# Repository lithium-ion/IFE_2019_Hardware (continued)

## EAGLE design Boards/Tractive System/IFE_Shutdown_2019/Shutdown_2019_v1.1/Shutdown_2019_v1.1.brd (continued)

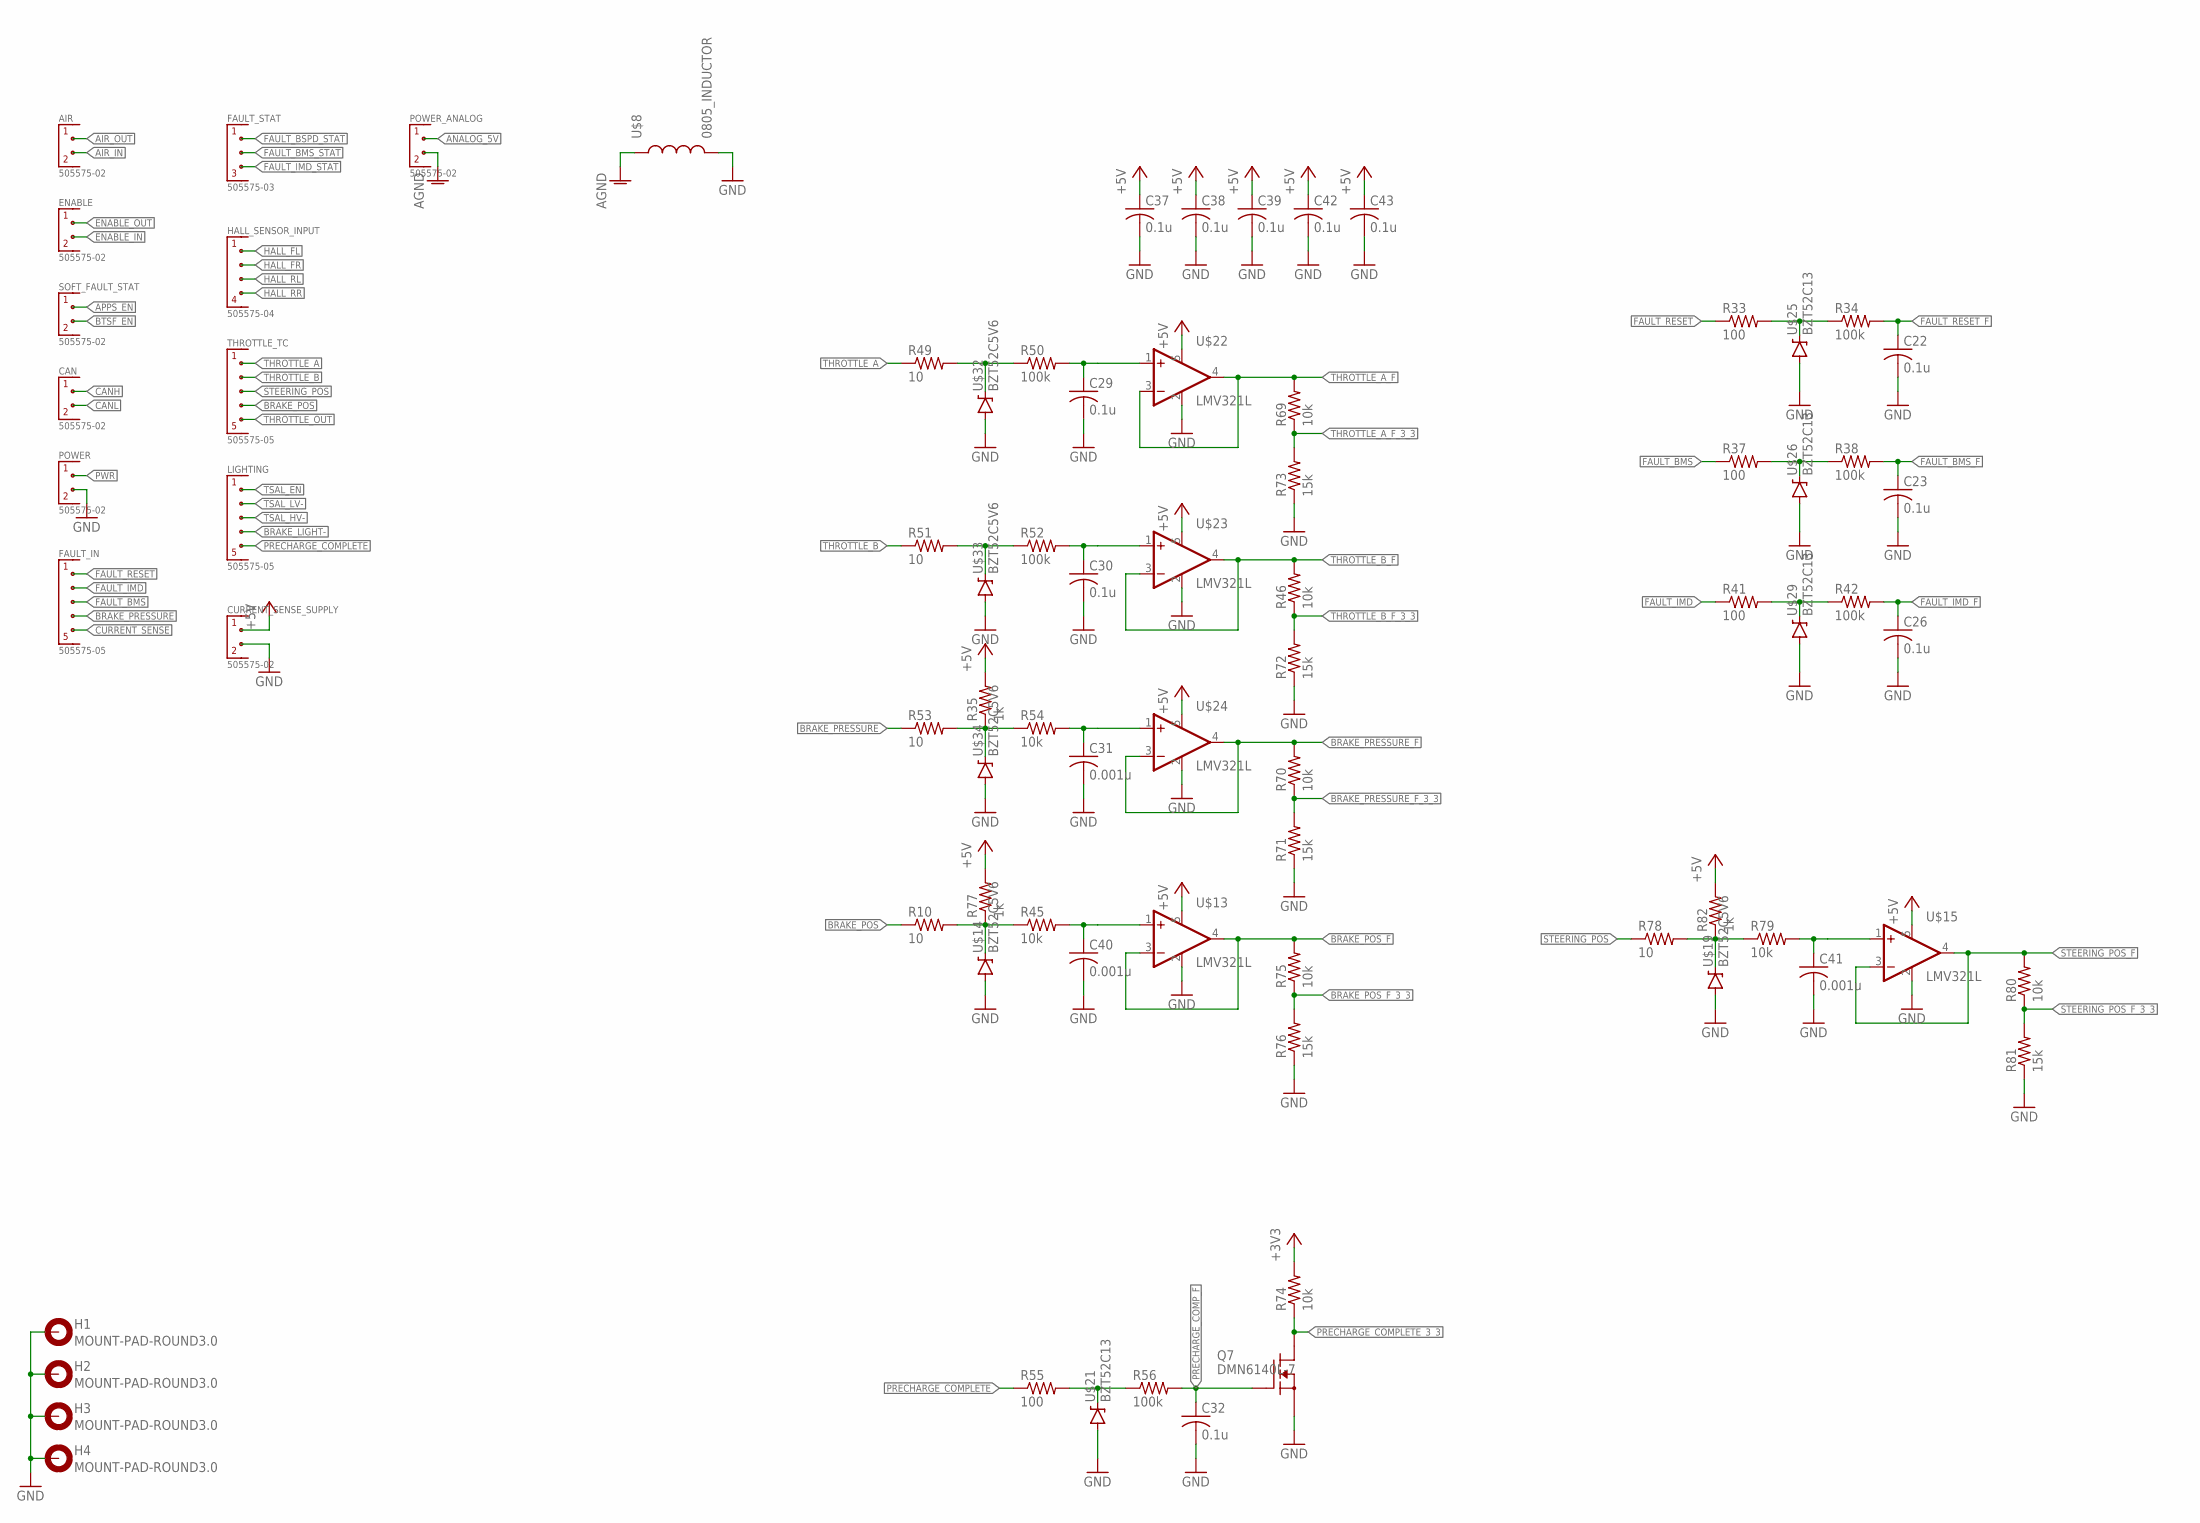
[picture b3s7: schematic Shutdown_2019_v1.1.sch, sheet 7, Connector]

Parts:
AIR: 505575-02
C22, C23, C26, C29, C30, C32: 0.1u; C0805
C31, C40, C41: 0.001u; C0805
C37, C38, C39, C42, C43: 0.1u; C0603
CAN: 505575-02
CURRENT_SENSE_SUPPLY: 505575-02
ENABLE: 505575-02
FAULT_IN: 505575-05
FAULT_STAT: 505575-03
H1, H2, H3, H4: MOUNT-PAD-ROUND3.0; 3,0-PAD
HALL_SENSOR_INPUT: 505575-04
LIGHTING: 505575-05
POWER: 505575-02
POWER_ANALOG: 505575-02
Q7: DMN6140L-7; SOT23
R10, R49, R51, R53, R78: 10; R0603
R33, R37, R41, R55: 100; R0603
R34, R38, R42, R50, R52, R56: 100k; R0603
R35, R77, R82: 1k; R0603
R45, R46, R54, R69, R70, R74, R75, R79, R80: 10k; R0603
R71, R72, R73, R76, R81: 15k; R0603
SOFT_FAULT_STAT: 505575-02
THROTTLE_TC: 505575-05
U$8: 0805_INDUCTOR; L0805
U$13, U$15, U$22, U$23, U$24: LMV321L; SOT23-5
U$14, U$19, U$32, U$33, U$34: BZT52C5V6; SOD-123
U$21, U$25, U$26, U$29: BZT52C13; SOD-123

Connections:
+3V3: R74.2; also elsewhere on the board
+5V: C37.1, C38.1, C39.1, C42.1, C43.1, CURRENT_SENSE_SUPPLY.1, R35.2, R77.2, R82.2, U$13.5 (VDD), U$15.5 (VDD), U$22.5 (VDD), U$23.5 (VDD), U$24.5 (VDD); also elsewhere on the board
AGND: POWER_ANALOG.2, U$8.1; also elsewhere on the board
AIR_IN: AIR.2; also elsewhere on the board
AIR_OUT: AIR.1; also elsewhere on the board
ANALOG_5V: POWER_ANALOG.1; also elsewhere on the board
APPS_EN: SOFT_FAULT_STAT.1; also elsewhere on the board
BRAKE_LIGHT-: LIGHTING.4; also elsewhere on the board
BRAKE_POS: R10.1, THROTTLE_TC.4
BRAKE_POS_F: R75.2, U$13.3 (-IN), U$13.4 (OUT)
BRAKE_POS_F_3_3: R75.1, R76.2; also elsewhere on the board
BRAKE_PRESSURE: FAULT_IN.4, R53.1
BRAKE_PRESSURE_F: R70.2, U$24.3 (-IN), U$24.4 (OUT); also elsewhere on the board
BRAKE_PRESSURE_F_3_3: R70.1, R71.2; also elsewhere on the board
BTSF_EN: SOFT_FAULT_STAT.2; also elsewhere on the board
CANH: CAN.1; also elsewhere on the board
CANL: CAN.2; also elsewhere on the board
CURRENT_SENSE: FAULT_IN.5; also elsewhere on the board
ENABLE_IN: ENABLE.2; also elsewhere on the board
ENABLE_OUT: ENABLE.1; also elsewhere on the board
FAULT_BMS: FAULT_IN.3, R37.1
FAULT_BMS_F: C23.1, R38.2; also elsewhere on the board
FAULT_BMS_STAT: FAULT_STAT.2; also elsewhere on the board
FAULT_BSPD_STAT: FAULT_STAT.1; also elsewhere on the board
FAULT_IMD: FAULT_IN.2, R41.1
FAULT_IMD_F: C26.1, R42.2; also elsewhere on the board
FAULT_IMD_STAT: FAULT_STAT.3; also elsewhere on the board
FAULT_RESET: FAULT_IN.1, R33.1
FAULT_RESET_F: C22.1, R34.2; also elsewhere on the board
GND: C22.2, C23.2, C26.2, C29.2, C30.2, C31.2, C32.2, C37.2, C38.2, C39.2, C40.2, C41.2, C42.2, C43.2, CURRENT_SENSE_SUPPLY.2, H1.B3,0, H2.B3,0, H3.B3,0, H4.B3,0, POWER.2, Q7.2 (S), R71.1, R72.1, R73.1, R76.1, R81.1, U$8.2, U$13.2 (GND), U$14.A, U$15.2 (GND), U$19.A, U$21.A, U$22.2 (GND), U$23.2 (GND), U$24.2 (GND), U$25.A, U$26.A, U$29.A, U$32.A, U$33.A, U$34.A; also elsewhere on the board
HALL_FL: HALL_SENSOR_INPUT.1; also elsewhere on the board
HALL_FR: HALL_SENSOR_INPUT.2; also elsewhere on the board
HALL_RL: HALL_SENSOR_INPUT.3; also elsewhere on the board
HALL_RR: HALL_SENSOR_INPUT.4; also elsewhere on the board
unnamed: R55.2, R56.1, U$21.C
unnamed: R10.2, R45.1, R77.1, U$14.C
unnamed: C40.1, R45.2, U$13.1 (+IN)
unnamed: R49.2, R50.1, U$32.C
unnamed: R78.2, R79.1, R82.1, U$19.C
unnamed: C41.1, R79.2, U$15.1 (+IN)
unnamed: R33.2, R34.1, U$25.C
unnamed: R37.2, R38.1, U$26.C
unnamed: C29.1, R50.2, U$22.1 (+IN)
unnamed: R41.2, R42.1, U$29.C
unnamed: R51.2, R52.1, U$33.C
unnamed: C30.1, R52.2, U$23.1 (+IN)
unnamed: R35.1, R53.2, R54.1, U$34.C
unnamed: C31.1, R54.2, U$24.1 (+IN)
PRECHARGE_COMPLETE: LIGHTING.5, R55.1
PRECHARGE_COMPLETE_3_3: Q7.3 (D), R74.1; also elsewhere on the board
PRECHARGE_COMP_F: C32.1, Q7.1 (G), R56.2
PWR: POWER.1; also elsewhere on the board
STEERING_POS: R78.1, THROTTLE_TC.3
STEERING_POS_F: R80.2, U$15.3 (-IN), U$15.4 (OUT)
STEERING_POS_F_3_3: R80.1, R81.2; also elsewhere on the board
THROTTLE_A: R49.1, THROTTLE_TC.1
THROTTLE_A_F: R69.2, U$22.3 (-IN), U$22.4 (OUT); also elsewhere on the board
THROTTLE_A_F_3_3: R69.1, R73.2; also elsewhere on the board
THROTTLE_B: R51.1, THROTTLE_TC.2
THROTTLE_B_F: R46.2, U$23.3 (-IN), U$23.4 (OUT)
THROTTLE_B_F_3_3: R46.1, R72.2; also elsewhere on the board
THROTTLE_OUT: THROTTLE_TC.5; also elsewhere on the board
TSAL_EN: LIGHTING.1; also elsewhere on the board
TSAL_HV-: LIGHTING.3; also elsewhere on the board
TSAL_LV-: LIGHTING.2; also elsewhere on the board

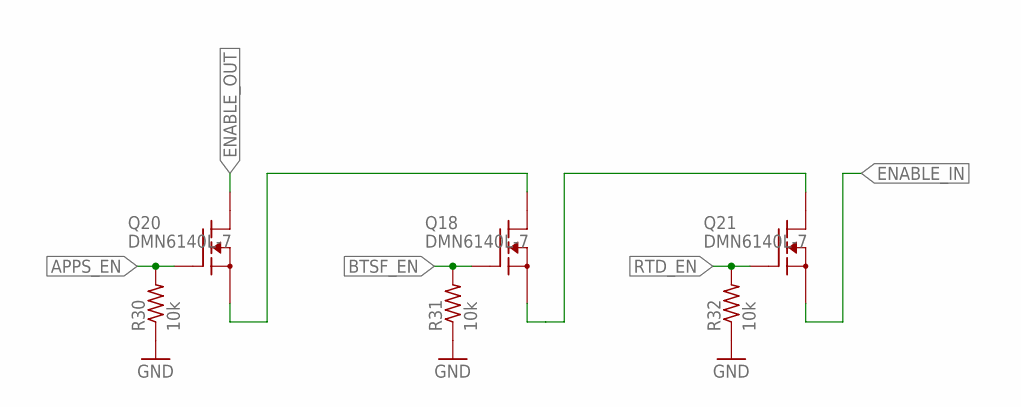
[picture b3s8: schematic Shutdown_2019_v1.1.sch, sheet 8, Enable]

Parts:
Q18, Q20, Q21: DMN6140L-7; SOT23
R30, R31, R32: 10k; R0603

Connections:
APPS_EN: Q20.1 (G), R30.2; also elsewhere on the board
BTSF_EN: Q18.1 (G), R31.2; also elsewhere on the board
ENABLE_IN: Q21.2 (S); also elsewhere on the board
ENABLE_OUT: Q20.3 (D); also elsewhere on the board
GND: R30.1, R31.1, R32.1; also elsewhere on the board
unnamed: Q18.3 (D), Q20.2 (S)
unnamed: Q18.2 (S), Q21.3 (D)
RTD_EN: Q21.1 (G), R32.2; also elsewhere on the board

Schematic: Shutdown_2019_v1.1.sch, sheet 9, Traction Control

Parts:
C16, C20: 1u; C0805
C21: 1u; C0603
C33, C34, C35, C36: 0.001u; C0805
D13: RED; LED-0603
JP2: PINHD-1X5; 1X05
R7: 50k; R0603
R28, R29, R47, R48, R58, R60, R62, R64: 10k; R0603
R57, R59, R61, R63: 10; R0603
R65, R66, R67, R68: 1k; R0603
U2: STM32F103CBT6; QFP50P900X900X160-48N
U$12: MCP4018; SOT23-6
U$18: LMV321L; SOT23-5
U$36, U$37, U$38, U$39: BZT52C5V6; SOD-123

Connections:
!RST_TC: JP2.2, R28.2, U2.7 (NRST)
+3V3: C16.1, C20.1, JP2.1, R28.1, R29.1, U2.9 (VDDA), U2.24 (VDD_1), U2.36 (VDD_2), U2.48 (VDD_3); also elsewhere on the board
+5V: R47.1, R48.1, R65.2, R66.2, R67.2, R68.2; also elsewhere on the board
AGND: C21.2, R7.1, U$12.2 (VSS), U$18.2 (GND); also elsewhere on the board
ANALOG_5V: C21.1, U$12.1 (VDD), U$18.5 (VDD); also elsewhere on the board
DEBUG_TC: D13.C, U2.2 (PC13-TAMPER-RTC)
GND: C16.2, C20.2, C33.2, C34.2, C35.2, C36.2, JP2.5, U2.8 (VSSA), U2.20 (PB2), U2.23 (VSS_1), U2.35 (VSS_2), U2.44 (BOOT0), U2.47 (VSS_3), U$36.A, U$37.A, U$38.A, U$39.A; also elsewhere on the board
HALL_FL: R57.1; also elsewhere on the board
HALL_FL_F: C33.1, R58.2, U2.11 (PA1)
HALL_FR: R59.1; also elsewhere on the board
HALL_FR_F: C34.1, R60.2, U2.10 (PA0-WKUP)
HALL_RL: R61.1; also elsewhere on the board
HALL_RL_F: C35.1, R62.2, U2.12 (PA2)
HALL_RR: R63.1; also elsewhere on the board
HALL_RR_F: C36.1, R64.2, U2.13 (PA3)
unnamed: R7.2, U$12.5 (B), U$18.1 (+IN)
unnamed: D13.A, R29.2
unnamed: R57.2, R58.1, R65.1, U$36.C
unnamed: R59.2, R60.1, R66.1, U$37.C
unnamed: R61.2, R62.1, R67.1, U$38.C
unnamed: R63.2, R64.1, R68.1, U$39.C
PA11: U2.32 (PA11)
SCL_TC: R48.2, U2.42 (PB6), U$12.3 (SCL)
SDA_TC: R47.2, U2.43 (PB7), U$12.4 (SDA)
SPI1_MISO: U2.17 (PA7); also elsewhere on the board
SPI1_MOSI: U2.16 (PA6); also elsewhere on the board
SPI1_NSS: U2.14 (PA4); also elsewhere on the board
SPI1_SCK: U2.15 (PA5); also elsewhere on the board
SWCLK_TC: JP2.4, U2.37 (PA14)
SWDIO_TC: JP2.3, U2.34 (PA13)
THROTTLE_A_F: U$12.6 (W); also elsewhere on the board
THROTTLE_OUT: U$18.3 (-IN), U$18.4 (OUT); also elsewhere on the board

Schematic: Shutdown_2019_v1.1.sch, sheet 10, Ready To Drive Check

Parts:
Q4: DMN6140L-7; SOT23
U$6: MAS806Q

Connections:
+12V: U$6.POS (A); also elsewhere on the board
GND: Q4.2 (S); also elsewhere on the board
unnamed: Q4.3 (D), U$6.NEG (B)
RTDS_EN: Q4.1 (G); also elsewhere on the board

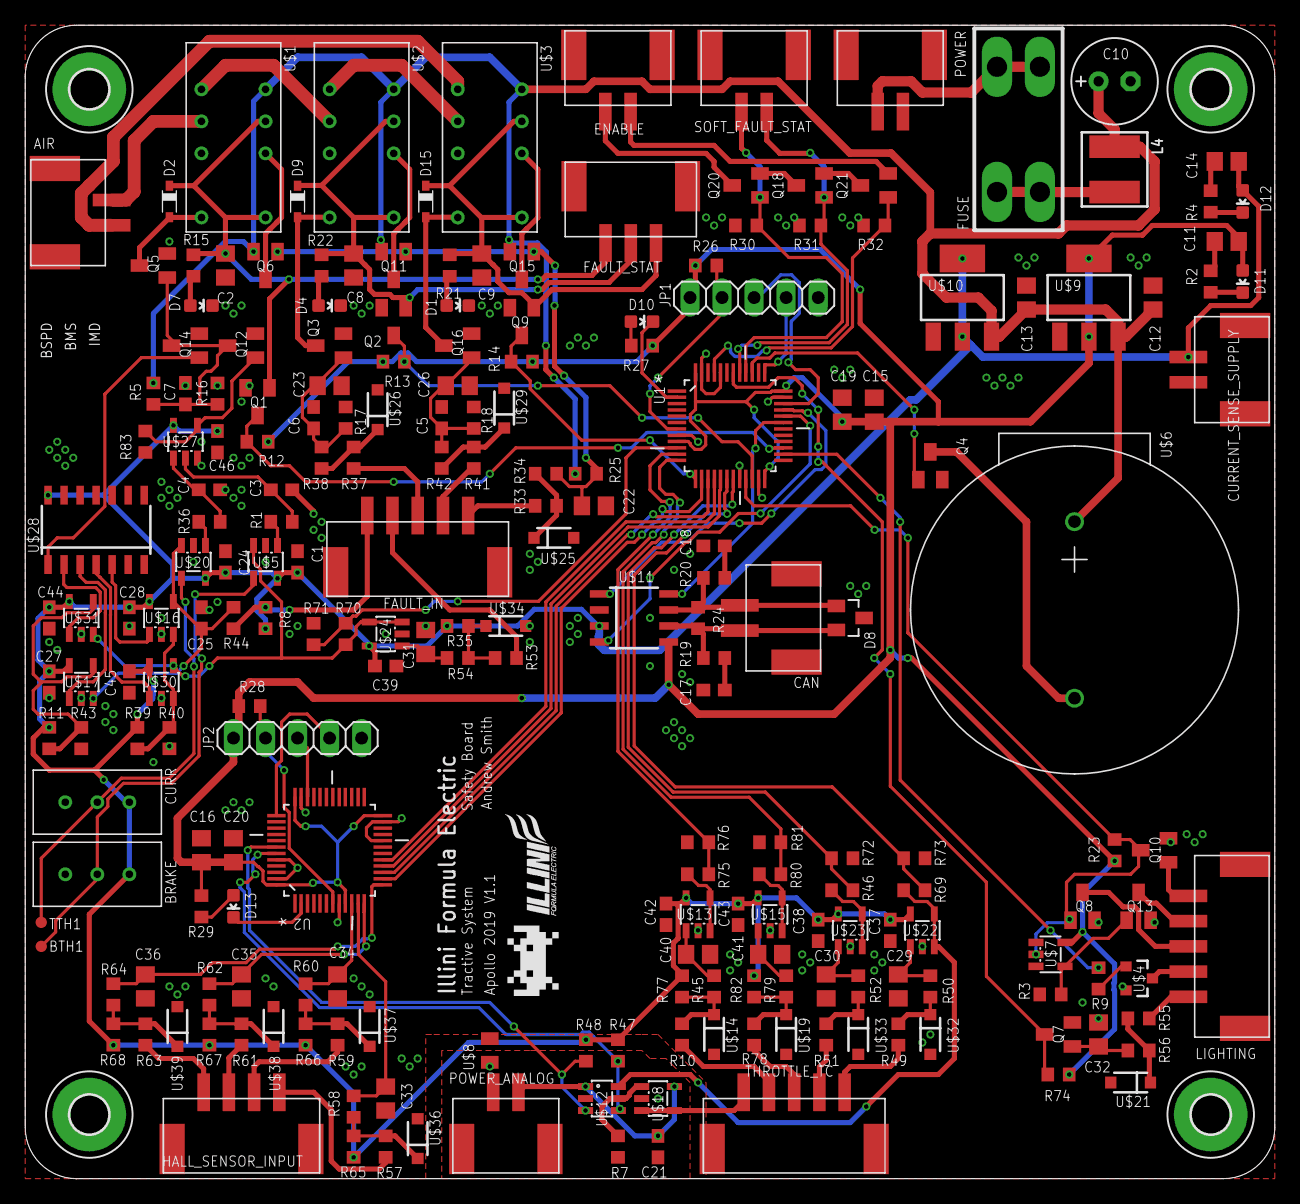
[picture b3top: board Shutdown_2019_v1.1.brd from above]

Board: 2 copper layers, 99.1 x 91.4 mm, 222 parts (0 on the bottom side), 138 nets.

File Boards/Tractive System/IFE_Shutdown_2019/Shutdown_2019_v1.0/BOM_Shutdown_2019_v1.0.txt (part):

Partlist exported from C:/Users/anges/Documents/IFE/IFE_2019_Hardware/Boards/Tractive System/IFE_Shutdown_2019/Shutdown_2019_v1.0/Shutdown_2019_v1.0.sch at 9/29/2018 3:35 PM

Qty Value              Device             Package                          Parts                                                                                    Description                                                             MPN           OC_FARNELL OC_NEWARK PACKAGE PROD_ID   SPICEPREFIX SUPPLIER           TP_SIGNAL_NAME VALUE
--2                      PINHD-1X5          1X05                             JP1, JP2                                                                                 PIN HEADER                                                                                                                                                                      
--5   0.001u             C-USC0805          C0805                            C31, C33, C34, C35, C36                                                                  CAPACITOR, American symbol                                                                                                   C                                                  
--1   0.01u              C-USC0603          C0603                            C25                                                                                      CAPACITOR, American symbol                                                                                                                                                      
--10  0.1u               C-USC0603          C0603                            C1, C5, C6, C7, C24, C27, C28, C37, C38, C39                                             CAPACITOR, American symbol                                                                                                                                                      
--6   0.1u               C-USC0805          C0805                            C22, C23, C26, C29, C30, C32                                                             CAPACITOR, American symbol                                                                                                   C                                                  
--7   10                 R-US_R0603         R0603                            R49, R51, R53, R57, R59, R61, R63                                                        RESISTOR, American symbol                                                                                                    R                                                  
--8   100                R-US_R0603         R0603                            R2, R4, R19, R20, R33, R37, R41, R55                                                     RESISTOR, American symbol                                                                                                    R                                                  
--2   100k               R-US_R0603         R0603                            R1, R36                                                                                  RESISTOR, American symbol                                                                                                                                                       
--6   100k               R-US_R0603         R0603                            R34, R38, R42, R50, R52, R56                                                             RESISTOR, American symbol                                                                                                    R                                                  
--11  10k                R-US_R0603         R0603                            R5, R8, R12, R13, R14, R16, R17, R18, R23, R39, R43                                      RESISTOR, American symbol                                                                                                                                                       
--18  10k                R-US_R0603         R0603                            R26, R27, R28, R29, R30, R31, R32, R46, R47, R48, R54, R58, R60, R62, R64, R69, R70, R74 RESISTOR, American symbol                                                                                                    R                                                  
--1   10u                INDUCTORNR5040     INDUCTOR_5X5MM_NR5040_NOTHERMALS L4                                                                                       Inductors                                                                                                                                                                       
--3   10uF               C-USC0805          C0805                            C2, C8, C9                                                                               CAPACITOR, American symbol                                                                                                   C                                                  
--1   120                R-US_R0603         R0603                            R24                                                                                      RESISTOR, American symbol                                                                                                    R                                                  
--3   15k                R-US_R0603         R0603                            R71, R72, R73                                                                            RESISTOR, American symbol                                                                                                    R                                                  
--3   1N914              1N914              SOD323-F                         D2, D9, D15                                                                                                                                                                                                                                                              
--4   1k                 R-US_R0603         R0603                            R11, R25, R40, R44                                                                       RESISTOR, American symbol                                                                                                                                                       
--6   1k                 R-US_R0603         R0603                            R9, R35, R65, R66, R67, R68                                                              RESISTOR, American symbol                                                                                                    R                                                  
--1   1u                 C-USC0603          C0603                            C21                                                                                      CAPACITOR, American symbol                                                                                                   C                                                  
--4   1u                 C-USC0805          C0805                            C15, C16, C19, C20                                                                       CAPACITOR, American symbol                                                                                                   C                                                  
--2   2.2u               C-USC0805          C0805                            C11, C14                                                                                 CAPACITOR, American symbol                                                                                                   C                                                  
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
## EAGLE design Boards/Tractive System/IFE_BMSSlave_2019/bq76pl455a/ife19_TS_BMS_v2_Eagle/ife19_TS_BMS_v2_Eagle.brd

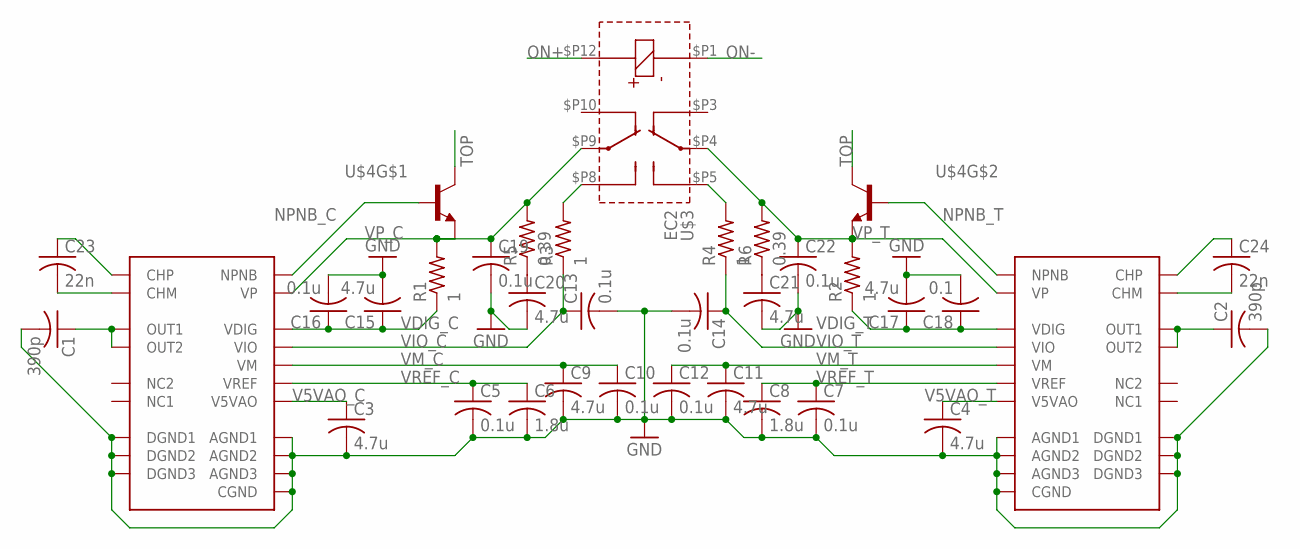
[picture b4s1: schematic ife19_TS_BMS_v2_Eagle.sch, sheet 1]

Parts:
C: BQ76PL455A; TQFP80
C1, C2: 390p; C0603K
C3, C4, C9, C11, C15, C17, C20, C21: 4.7u; C0603K
C5, C7, C10, C12, C13, C14, C16, C19, C22: 0.1u; C0603K
C6, C8: 1.8u; C0603K
C18: 0.1; C0603K
C23, C24: 22n; C0603
R1, R2, R3, R4: 1; R0603
R5, R6: 0.39; R0603
T: BQ76PL455A; TQFP80
U$3: EC2; DPDT_2.54
U$4: PHPT610030NK; LFPAK56D

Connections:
GND: C.30 (DGND1), C.35 (DGND2), C.37 (DGND3), C.48 (CGND), C.69 (AGND3), C.72 (AGND2), C.74 (AGND1), C1.2, C2.2, C3.2, C4.2, C5.2, C6.2, C7.2, C8.2, C9.2, C10.2, C11.2, C12.2, C13.2, C14.2, C15.2, C16.2, C17.2, C18.2, C19.2, C20.2, C21.2, C22.2, T.30 (DGND1), T.35 (DGND2), T.37 (DGND3), T.48 (CGND), T.69 (AGND3), T.72 (AGND2), T.74 (AGND1); also elsewhere on the board
unnamed: C.32 (CHP), C23.1
unnamed: C.33 (CHM), C23.2
unnamed: C.68 (OUT2), C.73 (OUT1), C1.1
unnamed: C2.1, T.68 (OUT2), T.73 (OUT1)
unnamed: C24.1, T.32 (CHP)
unnamed: C24.2, T.33 (CHM)
unnamed: R3.2, U$3.$P8
unnamed: R4.2, U$3.$P5
unnamed: C20.1, R5.1
unnamed: C21.1, R6.1
NPNB_C: C.71 (NPNB), U$4.B1 (B)
NPNB_T: T.71 (NPNB), U$4.B2 (B)
ON+: U$3.$P12; also elsewhere on the board
ON-: U$3.$P1; also elsewhere on the board
TOP: U$4.C1 (C), U$4.C2 (C)
V5VAO_C: C.58 (V5VAO), C3.1
V5VAO_T: C4.1, T.58 (V5VAO)
VDIG_C: C.34 (VDIG), C15.1, C16.1, R1.1
VDIG_T: C17.1, C18.1, R2.1, T.34 (VDIG)
VIO_C: C.41 (VIO), C13.1, R3.1
VIO_T: C14.1, R4.1, T.41 (VIO)
VM_C: C.31 (VM), C9.1, C10.1
VM_T: C11.1, C12.1, T.31 (VM)
VP_C: C.70 (VP), C19.1, R1.2, R5.2, U$3.$P9, U$4.E1 (E)
VP_T: C22.1, R2.2, R6.2, T.70 (VP), U$3.$P4, U$4.E2 (E)
VREF_C: C.67 (VREF), C5.1, C6.1
VREF_T: C7.1, C8.1, T.67 (VREF)

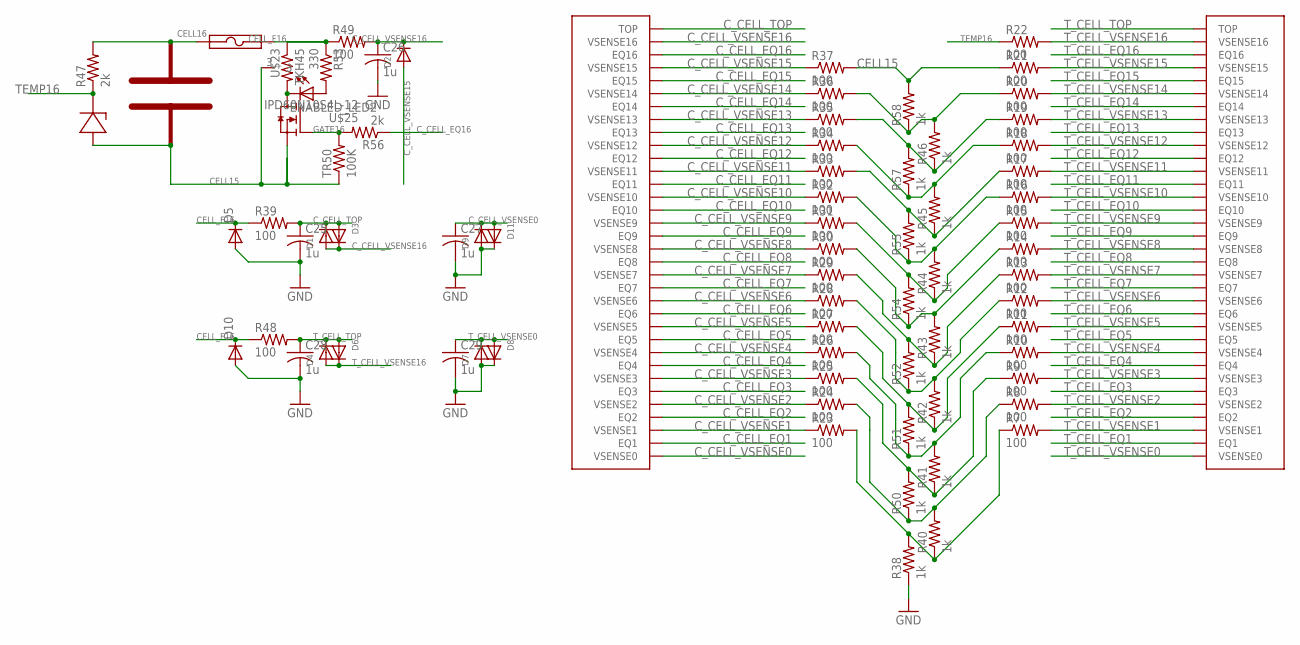
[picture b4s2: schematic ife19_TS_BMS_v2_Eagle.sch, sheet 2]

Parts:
C: BQ76PL455A; TQFP80
C25, C26, C27, C28, C29: 1u; C0603K
D1, D2, D3, D4, D6, D7, D8, D9, D11: DIODESOD-123; SOD-123
D5, D10: DIODE-DO214AC; DO214AC
ENABLED_LED2: LEDCHIPLED_0603; CHIPLED_0603
R7, R8, R9, R10, R11, R12, R13, R14, R15, R16, R17, R18, R19, R20, R21, R22, R23, R24, R25, R26, R27, R28, R29, R30, R31, R32, R33, R34, R35, R36, R37, R39, R48, R49: 100; R0603
R38, R40, R41, R42, R43, R44, R45, R46, R50, R51, R52, R54, R55, R57, R58: 1k; R0603
R47, R56: 2k; R0603
R53: 330; R0603
T: BQ76PL455A; TQFP80
TR50: 100K; R0603
U$1: LI6PT; 6PT
U$22: SF-0603FP; 0603
U$23: TKH45; TO252-TKH-45
U$25: IPD60N10S4L-12; TO252

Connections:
CELL15: R21.1, R37.2, R58.2, TR50.1, U$1.1 (TEMP-), U$1.CELLH- (CELL-), U$1.CELLP- (CELL-), U$23.3, U$25.3 (S)
CELL16: R47.2, U$1.CELLH+ (CELL+), U$1.CELLP+ (CELL+), U$22.1
CELL_F16: D5.C, D10.C, R39.1, R48.1, R49.1, R53.1, U$22.2, U$23.1
C_CELL_EQ1: C.28 (EQ1)
C_CELL_EQ2: C.26 (EQ2)
C_CELL_EQ3: C.24 (EQ3)
C_CELL_EQ4: C.22 (EQ4)
C_CELL_EQ5: C.20 (EQ5)
C_CELL_EQ6: C.18 (EQ6)
C_CELL_EQ7: C.16 (EQ7)
C_CELL_EQ8: C.14 (EQ8)
C_CELL_EQ9: C.12 (EQ9)
C_CELL_EQ10: C.10 (EQ10)
C_CELL_EQ11: C.8 (EQ11)
C_CELL_EQ12: C.6 (EQ12)
C_CELL_EQ13: C.4 (EQ13)
C_CELL_EQ14: C.2 (EQ14)
C_CELL_EQ15: C.80 (EQ15)
C_CELL_EQ16: C.78 (EQ16), R56.1
C_CELL_TOP: C.76 (TOP), C25.1, D1.C, D3.A, R39.2
C_CELL_VSENSE0: C.29 (VSENSE0), C27.1, D9.C, D11.A
C_CELL_VSENSE1: C.27 (VSENSE1), R23.1
C_CELL_VSENSE2: C.25 (VSENSE2), R24.1
C_CELL_VSENSE3: C.23 (VSENSE3), R25.1
C_CELL_VSENSE4: C.21 (VSENSE4), R26.1
C_CELL_VSENSE5: C.19 (VSENSE5), R27.1
C_CELL_VSENSE6: C.17 (VSENSE6), R28.1
C_CELL_VSENSE7: C.15 (VSENSE7), R29.1
C_CELL_VSENSE8: C.13 (VSENSE8), R30.1
C_CELL_VSENSE9: C.11 (VSENSE9), R31.1
C_CELL_VSENSE10: C.9 (VSENSE10), R32.1
C_CELL_VSENSE11: C.7 (VSENSE11), R33.1
C_CELL_VSENSE12: C.5 (VSENSE12), R34.1
C_CELL_VSENSE13: C.3 (VSENSE13), R35.1
C_CELL_VSENSE14: C.1 (VSENSE14), R36.1
C_CELL_VSENSE15: C.79 (VSENSE15), D2.A, R37.1
C_CELL_VSENSE16: C.77 (VSENSE16), C26.1, D1.A, D2.C, D3.C, R49.2
GATE16: R56.2, TR50.2, U$25.1 (G)
GND: C25.2, C26.2, C27.2, C28.2, C29.2, D5.A, D7.A, D8.C, D9.A, D10.A, D11.C, R38.1; also elsewhere on the board
unnamed: R20.1, R36.2, R46.2, R58.1
unnamed: R19.1, R35.2, R46.1, R57.2
unnamed: R18.1, R34.2, R45.2, R57.1
unnamed: R17.1, R33.2, R45.1, R55.2
unnamed: R16.1, R32.2, R44.2, R55.1
unnamed: R15.1, R31.2, R44.1, R54.2
unnamed: R14.1, R30.2, R43.2, R54.1
unnamed: R13.1, R29.2, R43.1, R52.2
unnamed: R12.1, R28.2, R42.2, R52.1
unnamed: R11.1, R27.2, R42.1, R51.2
unnamed: R10.1, R26.2, R41.2, R51.1
unnamed: R9.1, R25.2, R41.1, R50.2
unnamed: R8.1, R24.2, R40.2, R50.1
unnamed: R7.1, R23.2, R38.2, R40.1
unnamed: ENABLED_LED2.A, R53.2
unnamed: ENABLED_LED2.C, U$23.2, U$25.2 (D)
TEMP16: R22.1, R47.1, U$1.2 (TEMP+)
T_CELL_EQ1: T.28 (EQ1)
T_CELL_EQ2: T.26 (EQ2)
T_CELL_EQ3: T.24 (EQ3)
T_CELL_EQ4: T.22 (EQ4)
T_CELL_EQ5: T.20 (EQ5)
T_CELL_EQ6: T.18 (EQ6)
T_CELL_EQ7: T.16 (EQ7)
T_CELL_EQ8: T.14 (EQ8)
T_CELL_EQ9: T.12 (EQ9)
T_CELL_EQ10: T.10 (EQ10)
T_CELL_EQ11: T.8 (EQ11)
T_CELL_EQ12: T.6 (EQ12)
T_CELL_EQ13: T.4 (EQ13)
T_CELL_EQ14: T.2 (EQ14)
T_CELL_EQ15: T.80 (EQ15)
T_CELL_EQ16: T.78 (EQ16)
T_CELL_TOP: C28.1, D4.C, D6.A, R48.2, T.76 (TOP)
T_CELL_VSENSE0: C29.1, D7.C, D8.A, T.29 (VSENSE0)
T_CELL_VSENSE1: R7.2, T.27 (VSENSE1)
T_CELL_VSENSE2: R8.2, T.25 (VSENSE2)
T_CELL_VSENSE3: R9.2, T.23 (VSENSE3)
T_CELL_VSENSE4: R10.2, T.21 (VSENSE4)
T_CELL_VSENSE5: R11.2, T.19 (VSENSE5)
T_CELL_VSENSE6: R12.2, T.17 (VSENSE6)
T_CELL_VSENSE7: R13.2, T.15 (VSENSE7)
T_CELL_VSENSE8: R14.2, T.13 (VSENSE8)
T_CELL_VSENSE9: R15.2, T.11 (VSENSE9)
T_CELL_VSENSE10: R16.2, T.9 (VSENSE10)
T_CELL_VSENSE11: R17.2, T.7 (VSENSE11)
T_CELL_VSENSE12: R18.2, T.5 (VSENSE12)
T_CELL_VSENSE13: R19.2, T.3 (VSENSE13)
T_CELL_VSENSE14: R20.2, T.1 (VSENSE14)
T_CELL_VSENSE15: R21.2, T.79 (VSENSE15)
T_CELL_VSENSE16: D4.A, D6.C, R22.2, T.77 (VSENSE16)

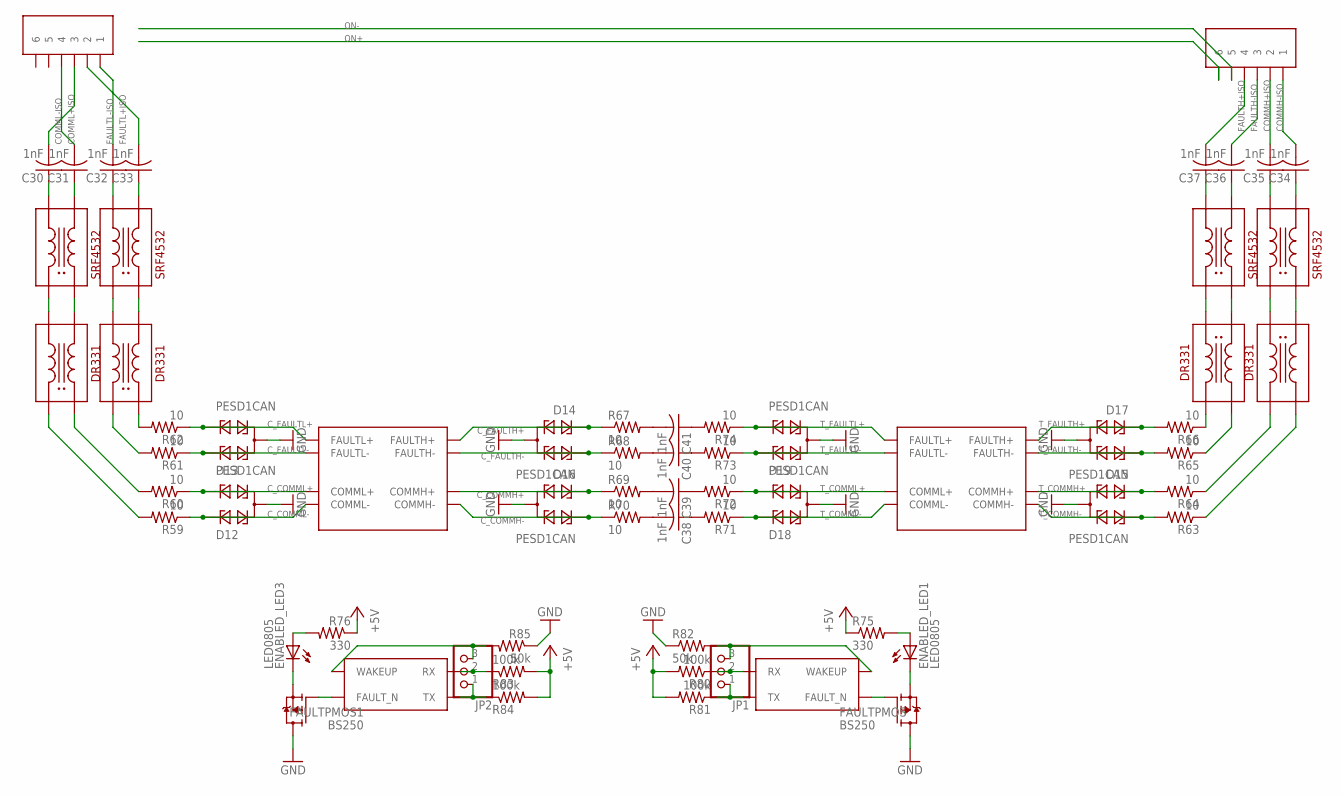
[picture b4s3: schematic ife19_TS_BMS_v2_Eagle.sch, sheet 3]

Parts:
C: BQ76PL455A; TQFP80
C30, C31, C32, C33, C34, C35, C36, C37, C38, C39, C40, C41: 1nF; C0805
D12, D13, D14, D15, D16, D17, D18, D19: PESD1CAN; SOT23
ENABLED_LED1, ENABLED_LED3: LED0805
FAULTPMOS, FAULTPMOS1: BS250; SOT23
JP1, JP2: PINHD-1X3CB; 1X03-CLEANBIG
R59, R60, R61, R62, R63, R64, R65, R66, R67, R68, R69, R70, R71, R72, R73, R74: 10; R0805
R75, R76: 330; R0805
R80, R81, R83, R84: 100k; R0805
R82, R85: 50k; R0805
T: BQ76PL455A; TQFP80
U$2, U$6, U$8, U$9: SRF5432
U$5, U$7: MICROFIT3.0-3P; 6POS-3MM
U$10, U$12, U$14, U$16: DR331

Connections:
COMMH+ISO: C35.2, U$7.P$2 (2)
COMMH-ISO: C34.2, U$7.P$1 (1)
COMML+ISO: C31.2, U$5.P$4 (4)
COMML-ISO: C30.2, U$5.P$3 (3)
C_COMMH+: C.55 (COMMH+), D16.1, R69.1
C_COMMH-: C.54 (COMMH-), D16.2, R70.1
C_COMML+: C.52 (COMML+), D12.2, R60.1
C_COMML-: C.53 (COMML-), D12.1, R59.1
C_FAULTH+: C.57 (FAULTH+), D14.1, R67.1
C_FAULTH-: C.56 (FAULTH-), D14.2, R68.1
C_FAULTL+: C.50 (FAULTL+), D13.2, R62.1
C_FAULTL-: C.51 (FAULTL-), D13.1, R61.1
FAULTH+ISO: C37.2, U$7.P$4 (4)
FAULTH-ISO: C36.2, U$7.P$3 (3)
FAULTL+ISO: C33.2, U$5.P$2 (2)
FAULTL-ISO: C32.2, U$5.P$1 (1)
FAULT_N: FAULTPMOS.1 (G), T.40 (FAULT_N)
GND: D12.3, D13.3, D14.3, D15.3, D16.3, D17.3, D18.3, D19.3, FAULTPMOS.3 (D), FAULTPMOS1.3 (D), R82.1, R85.1; also elsewhere on the board
unnamed: C30.1, U$2.P$3 (3)
unnamed: C31.1, U$2.P$2 (2)
unnamed: C32.1, U$6.P$3 (3)
unnamed: C33.1, U$6.P$2 (2)
unnamed: C34.1, U$9.P$2 (2)
unnamed: C35.1, U$9.P$3 (3)
unnamed: C36.1, U$8.P$2 (2)
unnamed: C37.1, U$8.P$3 (3)
unnamed: U$9.P$4 (4), U$14.P$2 (2)
unnamed: U$9.P$1 (1), U$14.P$1 (1)
unnamed: U$8.P$4 (4), U$16.P$2 (2)
unnamed: U$8.P$1 (1), U$16.P$1 (1)
unnamed: U$2.P$1 (1), U$10.P$3 (3)
unnamed: U$2.P$4 (4), U$10.P$4 (4)
unnamed: U$6.P$1 (1), U$12.P$3 (3)
unnamed: U$6.P$4 (4), U$12.P$4 (4)
unnamed: R62.2, U$12.P$2 (2)
unnamed: R66.1, U$16.P$3 (3)
unnamed: R61.2, U$12.P$1 (1)
unnamed: R60.2, U$10.P$2 (2)
unnamed: R59.2, U$10.P$1 (1)
unnamed: R65.1, U$16.P$4 (4)
unnamed: R64.1, U$14.P$3 (3)
unnamed: R63.1, U$14.P$4 (4)
unnamed: C41.2, R67.2
unnamed: C40.2, R68.2
unnamed: C39.2, R69.2
unnamed: C38.2, R70.2
unnamed: C38.1, R71.2
unnamed: C39.1, R72.2
unnamed: C40.1, R73.2
unnamed: C41.1, R74.2
unnamed: ENABLED_LED1.2 (C), FAULTPMOS.2 (S)
unnamed: ENABLED_LED1.1 (A), R75.2
unnamed: ENABLED_LED3.2 (C), FAULTPMOS1.2 (S)
unnamed: ENABLED_LED3.1 (A), R76.2
unnamed: C.40 (FAULT_N), FAULTPMOS1.1 (G)
unnamed: JP1.1, R81.1, T.38 (TX)
unnamed: JP1.3, R82.2, T.49 (WAKEUP)
unnamed: JP1.2, R80.1, T.39 (RX)
unnamed: C.38 (TX), JP2.1, R84.1
unnamed: C.49 (WAKEUP), JP2.3, R85.2
unnamed: C.39 (RX), JP2.2, R83.1
ON+: U$7.P$6 (6); also elsewhere on the board
ON-: U$7.P$5 (5); also elsewhere on the board
T_COMMH+: D15.1, R64.2, T.55 (COMMH+)
T_COMMH-: D15.2, R63.2, T.54 (COMMH-)
T_COMML+: D18.2, R72.1, T.52 (COMML+)
T_COMML-: D18.1, R71.1, T.53 (COMML-)
T_FAULTH+: D17.1, R66.2, T.57 (FAULTH+)
T_FAULTH-: D17.2, R65.2, T.56 (FAULTH-)
T_FAULTL+: D19.2, R74.1, T.50 (FAULTL+)
T_FAULTL-: D19.1, R73.1, T.51 (FAULTL-)
VIO: R75.1, R76.1, R80.2, R81.2, R83.2, R84.2

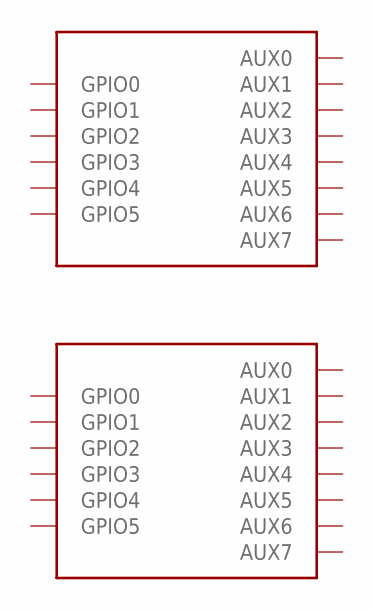
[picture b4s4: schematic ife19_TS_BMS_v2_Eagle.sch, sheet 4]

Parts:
C: BQ76PL455A; TQFP80
T: BQ76PL455A; TQFP80

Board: 4 copper layers, 168 parts (6 on the bottom side), 155 nets, no tracks yet.
